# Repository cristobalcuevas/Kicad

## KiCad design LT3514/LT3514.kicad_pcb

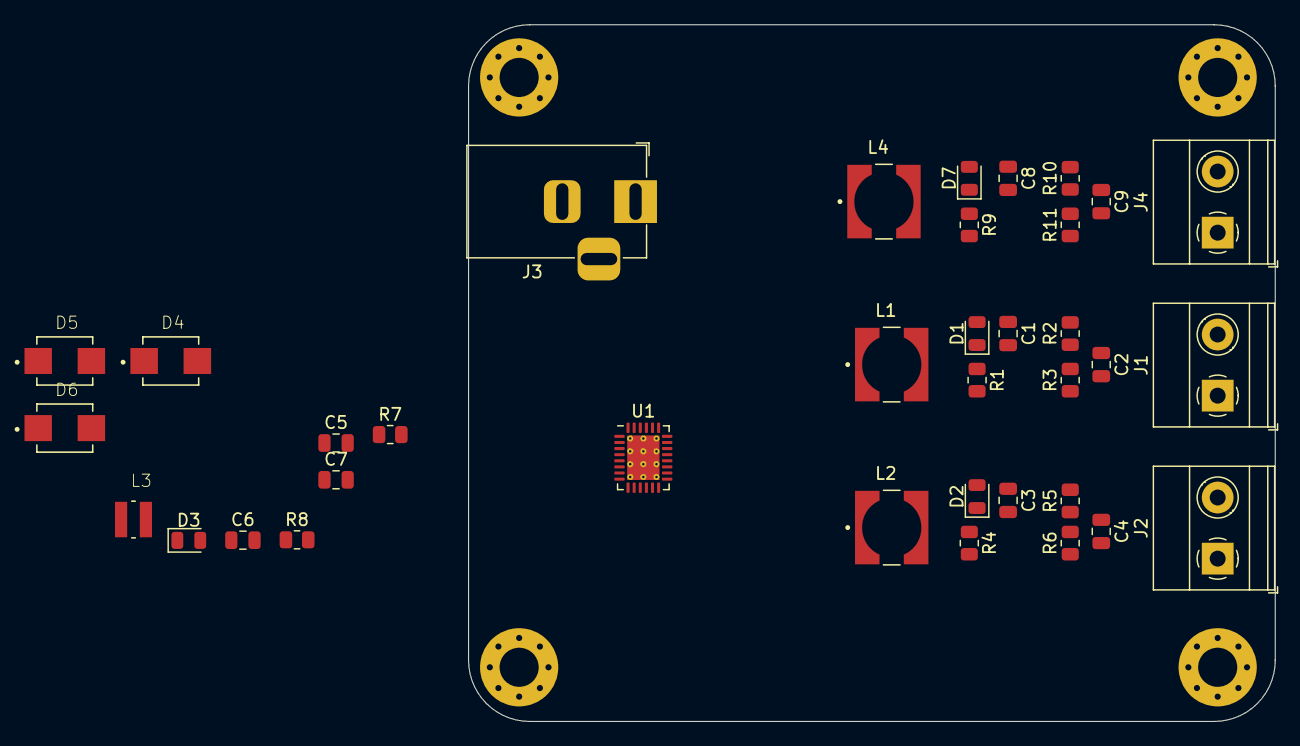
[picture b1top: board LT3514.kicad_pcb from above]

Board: 2 copper layers, 66.0 x 57.0 mm, 40 parts (0 on the bottom side), 23 nets, no tracks yet.

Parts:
C1: 47p; C_0805_2012Metric
C2: 47u; C_0805_2012Metric
C3: 22p; C_0805_2012Metric
C4, C9: 22u; C_0805_2012Metric
C5, C7: 1u; C_0805_2012Metric
C6: 47n; C_0805_2012Metric
C8: 100p; C_0805_2012Metric
D1, D2, D7: LED; LED_0805_2012Metric
D3: LED_Small; LED_0805_2012Metric
D4, D5, D6: D_Schottky_Small; B290
H1, H2, H3, H4: MountingHole; MountingHole_3.2mm_M3_Pad_Via
J1: OUT2; TerminalBlock_Phoenix_MKDS-1,5-2_1x02_P5.00mm_Horizontal
J2: OUT3; TerminalBlock_Phoenix_MKDS-1,5-2_1x02_P5.00mm_Horizontal
J3: Barrel_Jack_Switch; BarrelJack_Horizontal
J4: OUT1; TerminalBlock_Phoenix_MKDS-1,5-2_1x02_P5.00mm_Horizontal
L1: 4.7u; MSS6132
L2: 8.2u; MSS6132
L3: 10u; EPL3015
L4: 3.3u; MSS6132
R1, R4, R7, R9: 2k; R_0805_2012Metric
R2: 31.6k; R_0805_2012Metric
R3, R6, R11: 10.2k; R_0805_2012Metric
R5: 53.6k; R_0805_2012Metric
R8: 18.2k; R_0805_2012Metric
R10: 12.7k; R_0805_2012Metric
U1: LT3514xUFD; QFN-28-1EP_4x5mm_P0.5mm_EP2.65x3.65mm_ThermalVias

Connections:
+1V8: C8.1, C9.1, D7.2, J4.2, L4.2, R10.2
+3V3: C1.1, C2.1, D1.2, J1.2, L1.2, R2.2
+5V: C3.1, C4.1, D2.2, J2.2, L2.2, R5.2
+12V: C5.1, C7.2, J3.1, L3.1, R7.1, U1.9, U1.11, U1.16, U1.26, U1.28
/1V8/FB1: C8.2, R10.1, R11.2, U1.20
/1V8/SW1: D4.1, L4.1, U1.5
/3V3/FB3: C1.2, R2.1, R3.2, U1.21
/3V3/SW3: D5.1, L1.1, U1.4
/5V0/FB4: C3.2, R5.1, R6.2, U1.19
/5V0/SW4: D6.1, L2.1, U1.7
GND: C2.2, C4.2, C5.2, C6.2, C9.2, J1.1, J2.1, J3.2, J3.3, J4.1, R1.2, R3.1, R4.2, R6.1, R8.1, R9.2, R11.1, U1.10, U1.18, U1.27, U1.29
unnamed: C6.1, U1.12, U1.13, U1.15
unnamed: C7.1, U1.25
unnamed: D1.1, R1.1
unnamed: D2.1, R4.1
unnamed: D3.1, U1.23
unnamed: D3.2, R7.2
unnamed: D4.2, U1.6
unnamed: D5.2, U1.3
unnamed: D6.2, U1.8
unnamed: D7.1, R9.1
unnamed: L3.2, U1.24
unnamed: R8.2, U1.17

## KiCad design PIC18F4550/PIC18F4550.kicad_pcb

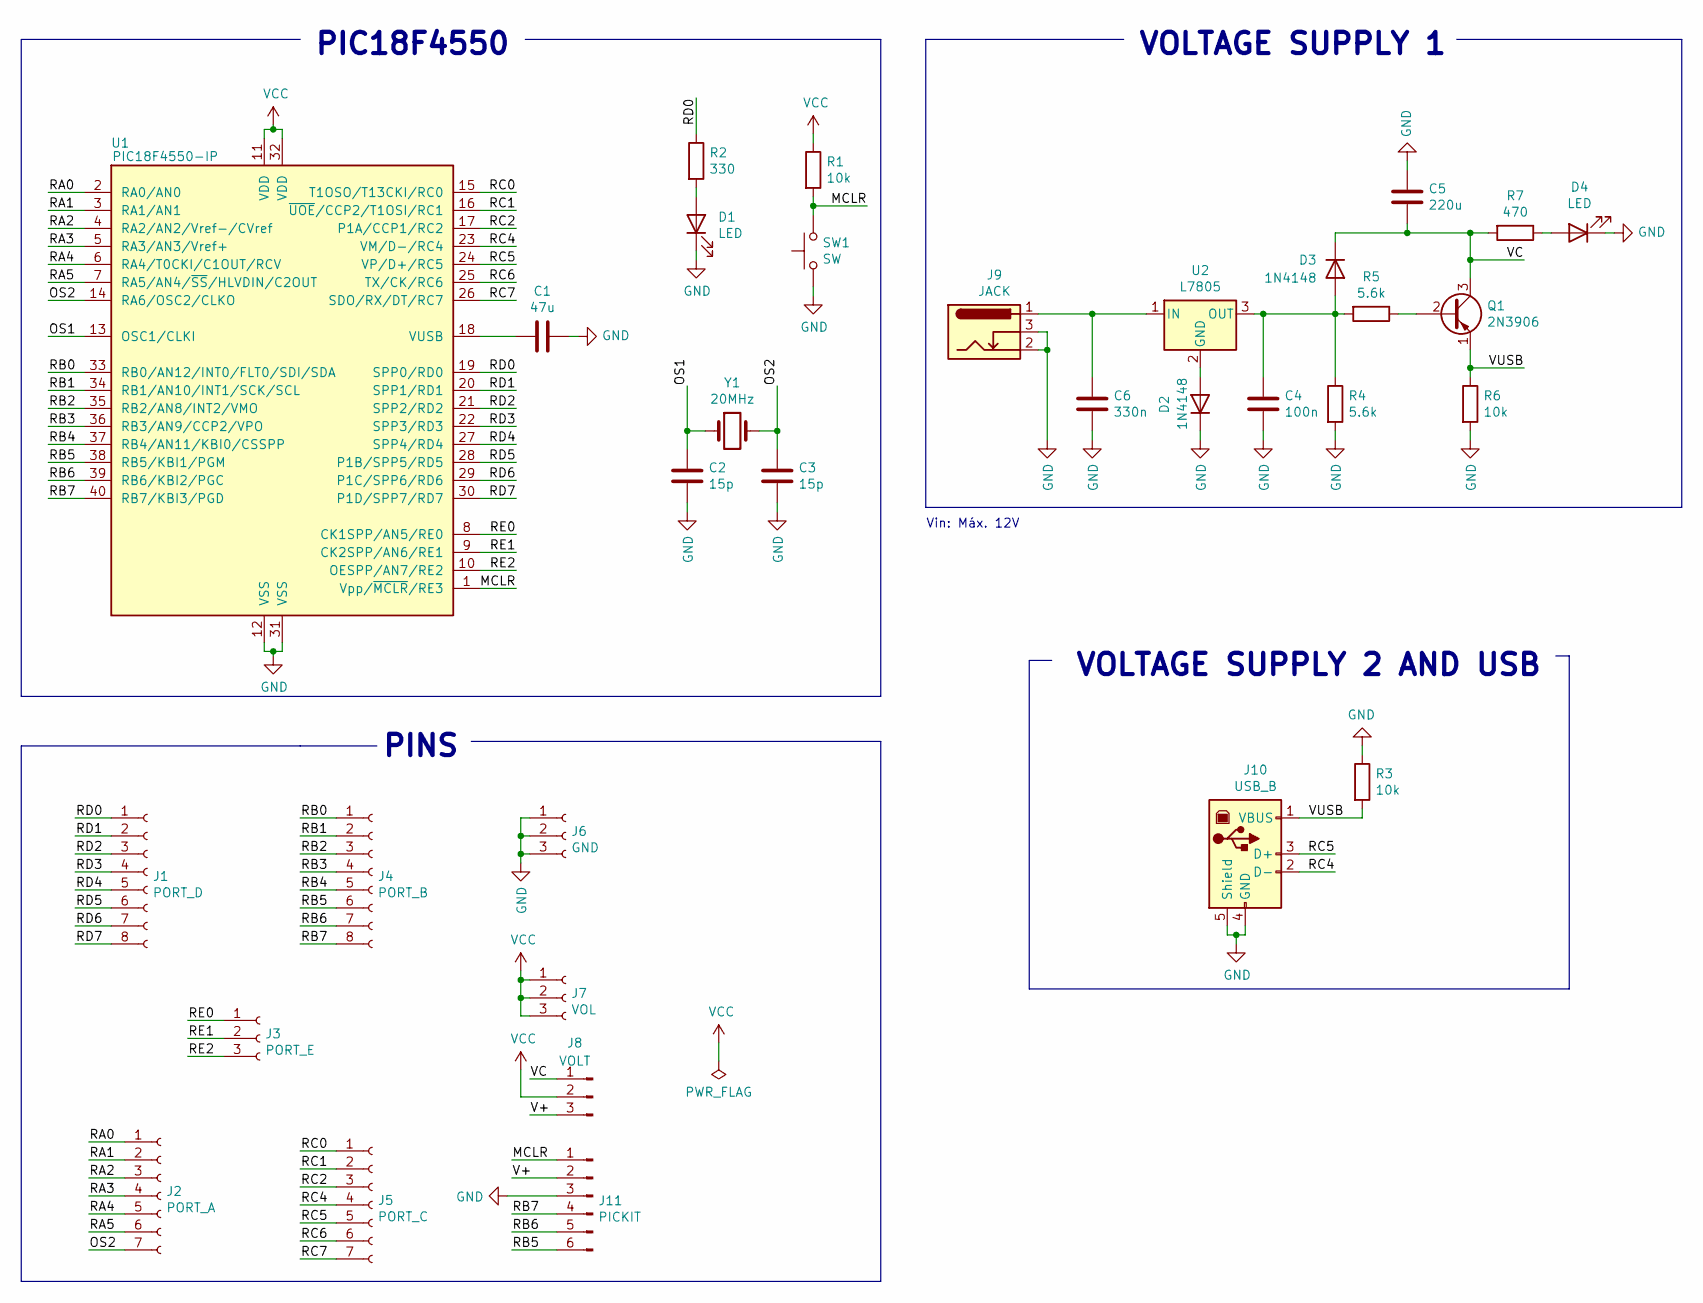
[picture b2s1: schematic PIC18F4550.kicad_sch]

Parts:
C1: 47u; CP_Radial_D6.3mm_P2.50mm
C2, C3: 15p; C_Disc_D3.8mm_W2.6mm_P2.50mm
C4: 100n; C_Disc_D3.8mm_W2.6mm_P2.50mm
C5: 220u; CP_Radial_D10.0mm_P2.50mm
C6: 330n; C_Disc_D3.8mm_W2.6mm_P2.50mm
D1, D4: LED; LED_D5.0mm
D2, D3: 1N4148; D_DO-35_SOD27_P7.62mm_Horizontal
J1: PORT_D; PinSocket_1x08_P2.54mm_Vertical
J2: PORT_A; PinSocket_1x07_P2.54mm_Vertical
J3: PORT_E; PinSocket_1x03_P2.54mm_Vertical
J4: PORT_B; PinSocket_1x08_P2.54mm_Vertical
J5: PORT_C; PinSocket_1x07_P2.54mm_Vertical
J6: GND; PinSocket_1x03_P2.54mm_Vertical
J7: VOL; PinSocket_1x03_P2.54mm_Vertical
J8: VOLT; PinHeader_1x03_P2.54mm_Vertical
J9: JACK; BarrelJack_Horizontal
J10: USB_B; USB_B_OST_USB-B1HSxx_Horizontal
J11: PICKIT; PinHeader_1x06_P2.54mm_Vertical
Q1: 2N3906; TO-92_Inline
R1, R3, R6: 10k; R_Axial_DIN0207_L6.3mm_D2.5mm_P7.62mm_Horizontal
R2: 330; R_Axial_DIN0207_L6.3mm_D2.5mm_P7.62mm_Horizontal
R4, R5: 5.6k; R_Axial_DIN0207_L6.3mm_D2.5mm_P7.62mm_Horizontal
R7: 470; R_Axial_DIN0207_L6.3mm_D2.5mm_P7.62mm_Horizontal
SW1: SW; SW_PUSH_6mm
U1: PIC18F4550-IP; DIP-40_W15.24mm
U2: L7805; TO-220-3_Vertical
Y1: 20MHz; Crystal_HC50_Vertical

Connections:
/MCLR: J11.1, R1.2, SW1.2, U1.1 (Vpp/~MCLR/RE3)
/OS1: C2.1, U1.13 (OSC1/CLKI), Y1.1
/OS2: C3.1, J2.7, U1.14 (RA6/OSC2/CLKO), Y1.2
/RA0: J2.1, U1.2 (RA0/AN0)
/RA1: J2.2, U1.3 (RA1/AN1)
/RA2: J2.3, U1.4 (RA2/AN2/Vref-/CVref)
/RA3: J2.4, U1.5 (RA3/AN3/Vref+)
/RA4: J2.5, U1.6 (RA4/T0CKI/C1OUT/RCV)
/RA5: J2.6, U1.7 (RA5/AN4/~SS/HLVDIN/C2OUT)
/RB0: J4.1, U1.33 (RB0/AN12/INT0/FLT0/SDI/SDA)
/RB1: J4.2, U1.34 (RB1/AN10/INT1/SCK/SCL)
/RB2: J4.3, U1.35 (RB2/AN8/INT2/VMO)
/RB3: J4.4, U1.36 (RB3/AN9/CCP2/VPO)
/RB4: J4.5, U1.37 (RB4/AN11/KBI0/CSSPP)
/RB5: J4.6, J11.6, U1.38 (RB5/KBI1/PGM)
/RB6: J4.7, J11.5, U1.39 (RB6/KBI2/PGC)
/RB7: J4.8, J11.4, U1.40 (RB7/KBI3/PGD)
/RC0: J5.1, U1.15 (T1OSO/T13CKI/RC0)
/RC1: J5.2, U1.16 (~UOE/CCP2/T1OSI/RC1)
/RC2: J5.3, U1.17 (P1A/CCP1/RC2)
/RC4: J5.4, J10.2 (D-), U1.23 (VM/D-/RC4)
/RC5: J5.5, J10.3 (D+), U1.24 (VP/D+/RC5)
/RC6: J5.6, U1.25 (TX/CK/RC6)
/RC7: J5.7, U1.26 (SDO/RX/DT/RC7)
/RD0: J1.1, R2.1, U1.19 (SPP0/RD0)
/RD1: J1.2, U1.20 (SPP1/RD1)
/RD2: J1.3, U1.21 (SPP2/RD2)
/RD3: J1.4, U1.22 (SPP3/RD3)
/RD4: J1.5, U1.27 (SPP4/RD4)
/RD5: J1.6, U1.28 (P1B/SPP5/RD5)
/RD6: J1.7, U1.29 (P1C/SPP6/RD6)
/RD7: J1.8, U1.30 (P1D/SPP7/RD7)
/RE0: J3.1, U1.8 (CK1SPP/AN5/RE0)
/RE1: J3.2, U1.9 (CK2SPP/AN6/RE1)
/RE2: J3.3, U1.10 (OESPP/AN7/RE2)
/V+: J8.3, J11.2
/VC: C5.2, D3.1 (K), J8.1, Q1.3 (C), R7.2
/VUSB: J10.1 (VBUS), Q1.1 (E), R3.2, R6.1
GND: C1.1, C2.2, C3.2, C4.2, C5.1, C6.2, D1.1 (K), D2.1 (K), D4.1 (K), J6.1, J6.2, J6.3, J9.2, J9.3, J10.4 (GND), J10.5 (Shield), J11.3, R3.1, R4.2, R6.2, SW1.1, U1.12 (VSS), U1.31 (VSS)
unnamed: C1.2, U1.18 (VUSB)
unnamed: C4.1, D3.2 (A), R4.1, R5.2, U2.3 (OUT)
unnamed: C6.1, J9.1, U2.1 (IN)
unnamed: D1.2 (A), R2.2
unnamed: D2.2 (A), U2.2 (GND)
unnamed: D4.2 (A), R7.1
unnamed: Q1.2 (B), R5.1
VCC: J7.1, J7.2, J7.3, J8.2, R1.1, U1.11 (VDD), U1.32 (VDD)

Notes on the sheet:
PINS
Vin: Máx. 12V
VOLTAGE SUPPLY 1
VOLTAGE SUPPLY 2 AND USB
PIC18F4550

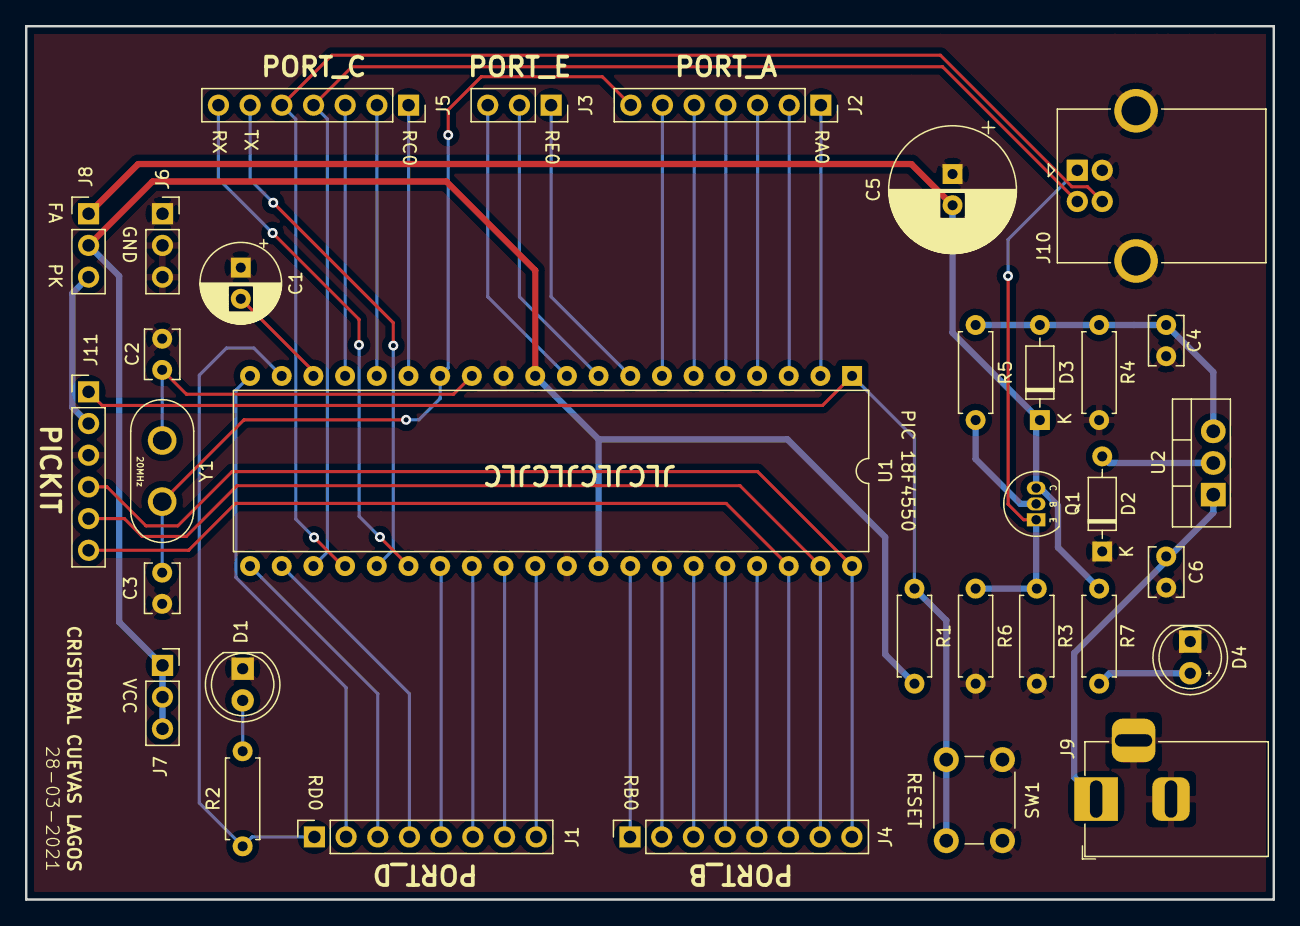
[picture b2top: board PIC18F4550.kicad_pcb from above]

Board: 2 copper layers, 100.0 x 70.0 mm, 33 parts (0 on the bottom side), 47 nets.

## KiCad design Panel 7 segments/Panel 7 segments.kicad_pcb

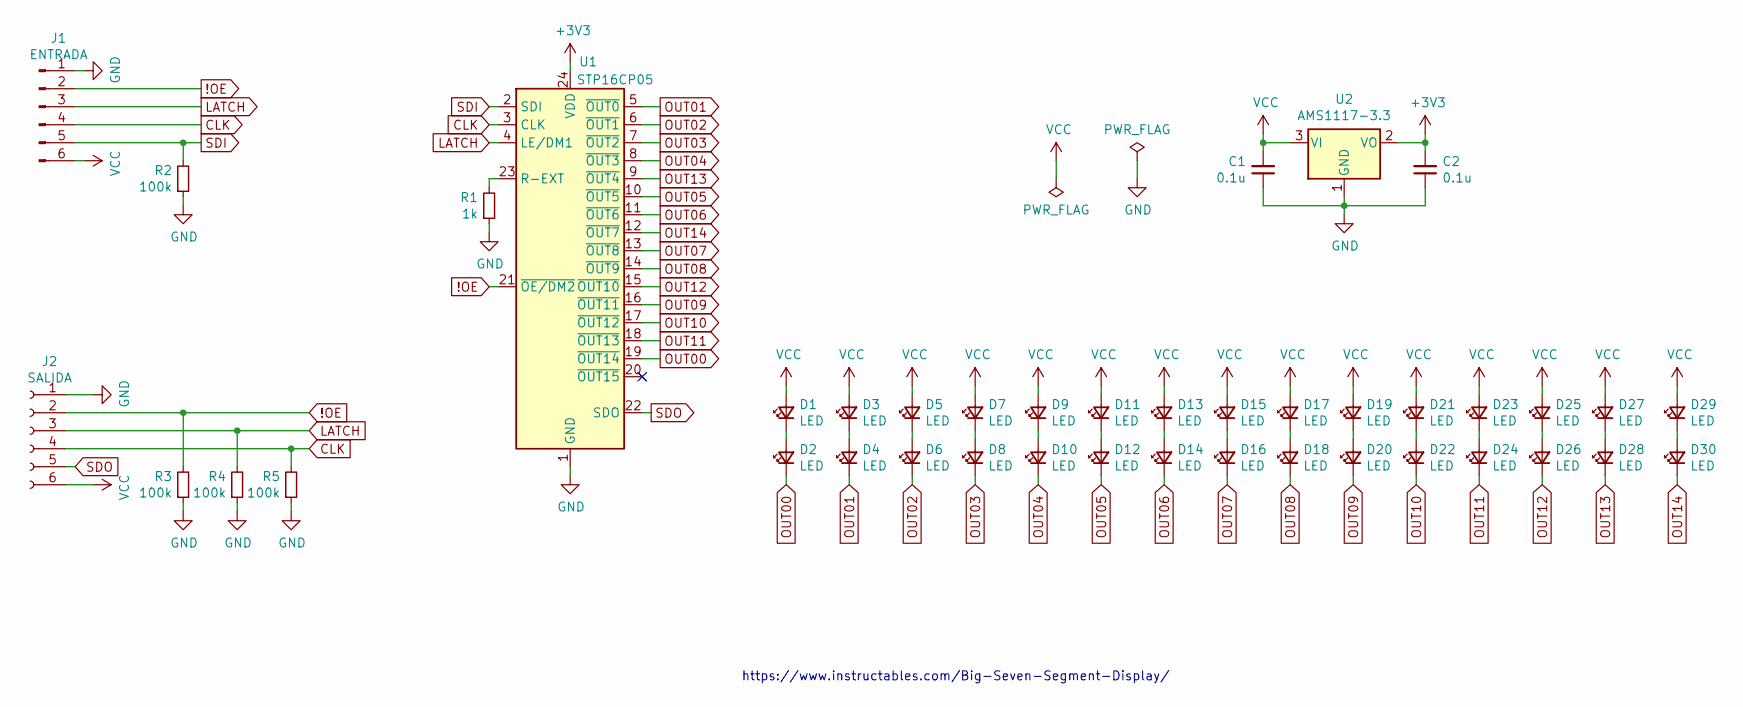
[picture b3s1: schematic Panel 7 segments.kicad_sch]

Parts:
C1, C2: 0.1u; C_1206_3216Metric
D1, D2, D3, D4, D5, D6, D7, D8, D9, D10, D11, D12, D13, D14, D15, D16, D17, D18, D19, D20, D21, D22, D23, D24, D25, D26, D27, D28, D29, D30: LED; LED_2010_5025Metric
J1: ENTRADA; PinHeader_1x06_P2.54mm_Horizontal
J2: SALIDA; PinSocket_1x06_P2.54mm_Horizontal
R1: 1k; R_1206_3216Metric
R2, R3, R4, R5: 100k; R_1206_3216Metric
U1: STP16CP05; TSSOP-24_4.4x7.8mm_P0.65mm
U2: AMS1117-3.3; SOT-223-3_TabPin2

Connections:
!OE: J1.2, J2.2, R3.2, U1.21 (~OE/DM2)
+3V3: C2.2, U1.24 (VDD), U2.2 (VO)
CLK: J1.4, J2.4, R5.2, U1.3 (CLK)
GND: C1.1, C2.1, J1.1, J2.1, R1.1, R2.1, R3.1, R4.1, R5.1, U1.1 (GND), U2.1 (GND)
LATCH: J1.3, J2.3, R4.2, U1.4 (LE/DM1)
unnamed: D1.1 (K), D2.2 (A)
unnamed: D3.1 (K), D4.2 (A)
unnamed: D5.1 (K), D6.2 (A)
unnamed: D7.1 (K), D8.2 (A)
unnamed: D9.1 (K), D10.2 (A)
unnamed: D11.1 (K), D12.2 (A)
unnamed: D13.1 (K), D14.2 (A)
unnamed: D15.1 (K), D16.2 (A)
unnamed: D17.1 (K), D18.2 (A)
unnamed: D19.1 (K), D20.2 (A)
unnamed: D21.1 (K), D22.2 (A)
unnamed: D23.1 (K), D24.2 (A)
unnamed: D25.1 (K), D26.2 (A)
unnamed: D27.1 (K), D28.2 (A)
unnamed: D29.1 (K), D30.2 (A)
unnamed: R1.2, U1.23 (R-EXT)
OUT00: D2.1 (K), U1.19 (~OUT14)
OUT01: D4.1 (K), U1.5 (~OUT0)
OUT02: D6.1 (K), U1.6 (~OUT1)
OUT03: D8.1 (K), U1.7 (~OUT2)
OUT04: D10.1 (K), U1.8 (~OUT3)
OUT05: D12.1 (K), U1.10 (~OUT5)
OUT06: D14.1 (K), U1.11 (~OUT6)
OUT07: D16.1 (K), U1.13 (~OUT8)
OUT08: D18.1 (K), U1.14 (~OUT9)
OUT09: D20.1 (K), U1.16 (~OUT11)
OUT10: D22.1 (K), U1.17 (~OUT12)
OUT11: D24.1 (K), U1.18 (~OUT13)
OUT12: D26.1 (K), U1.15 (~OUT10)
OUT13: D28.1 (K), U1.9 (~OUT4)
OUT14: D30.1 (K), U1.12 (~OUT7)
SDI: J1.5, R2.2, U1.2 (SDI)
SDO: J2.5, U1.22 (SDO)
VCC: C1.2, D1.2 (A), D3.2 (A), D5.2 (A), D7.2 (A), D9.2 (A), D11.2 (A), D13.2 (A), D15.2 (A), D17.2 (A), D19.2 (A), D21.2 (A), D23.2 (A), D25.2 (A), D27.2 (A), D29.2 (A), J1.6, J2.6, U2.3 (VI)

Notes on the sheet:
https://www.instructables.com/Big-Seven-Segment-Display/

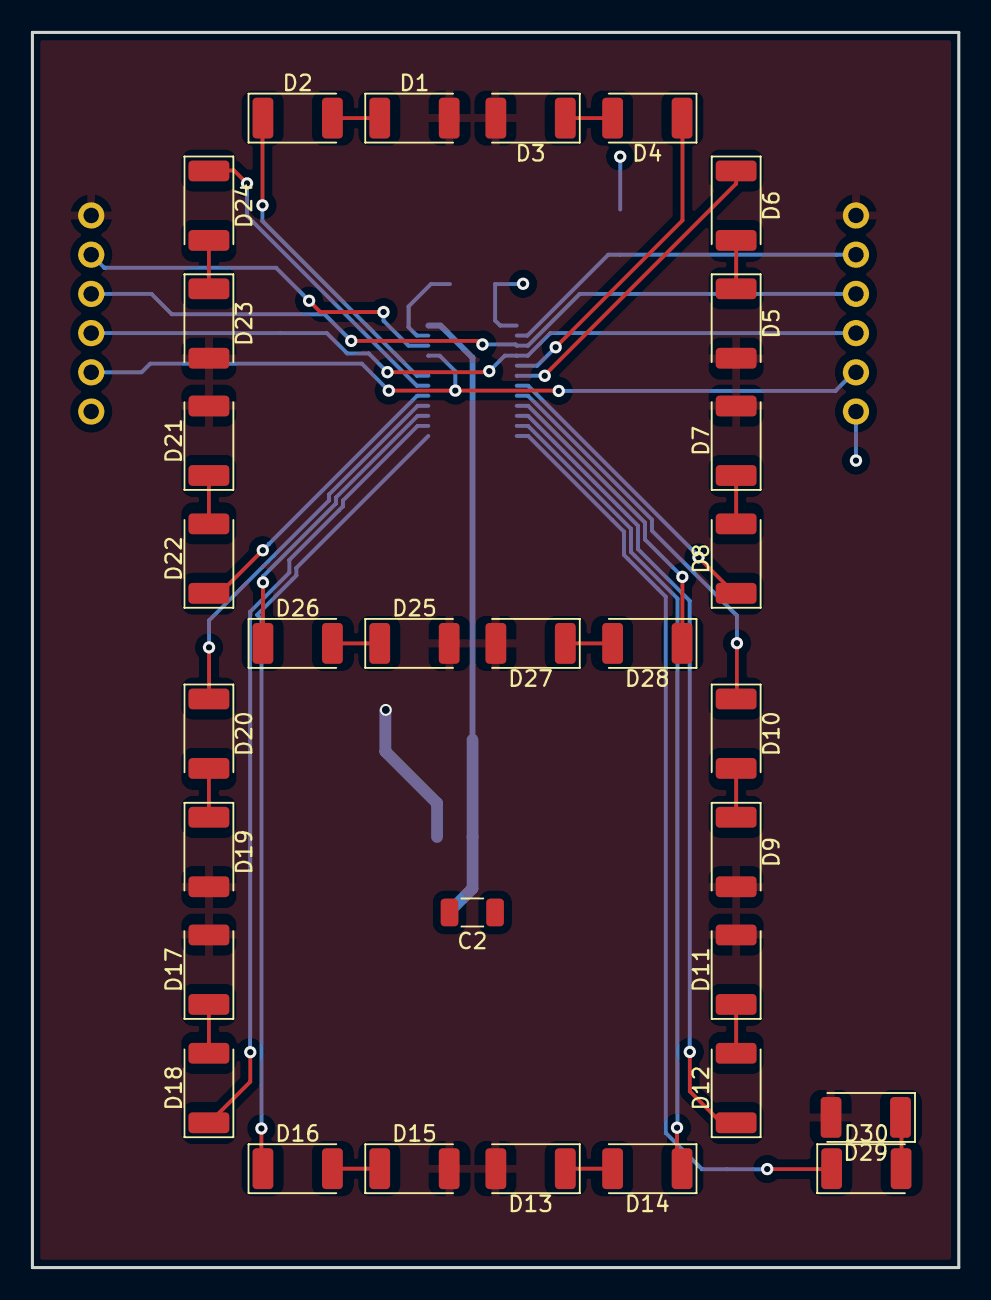
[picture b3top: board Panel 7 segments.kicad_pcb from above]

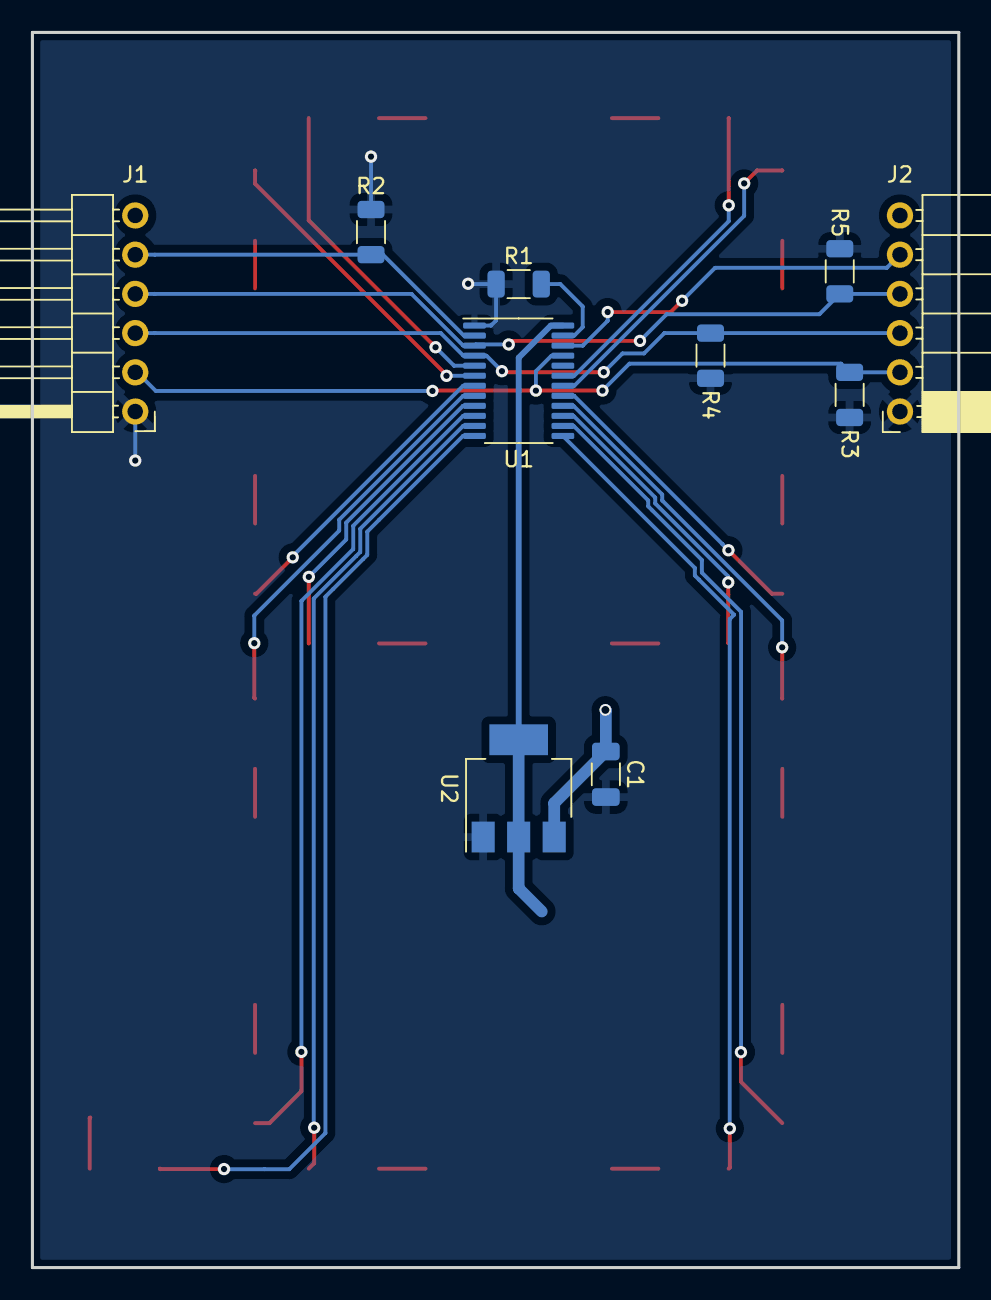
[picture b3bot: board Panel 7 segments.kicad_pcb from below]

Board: 2 copper layers, 60.0 x 80.0 mm, 41 parts (10 on the bottom side), 39 nets.

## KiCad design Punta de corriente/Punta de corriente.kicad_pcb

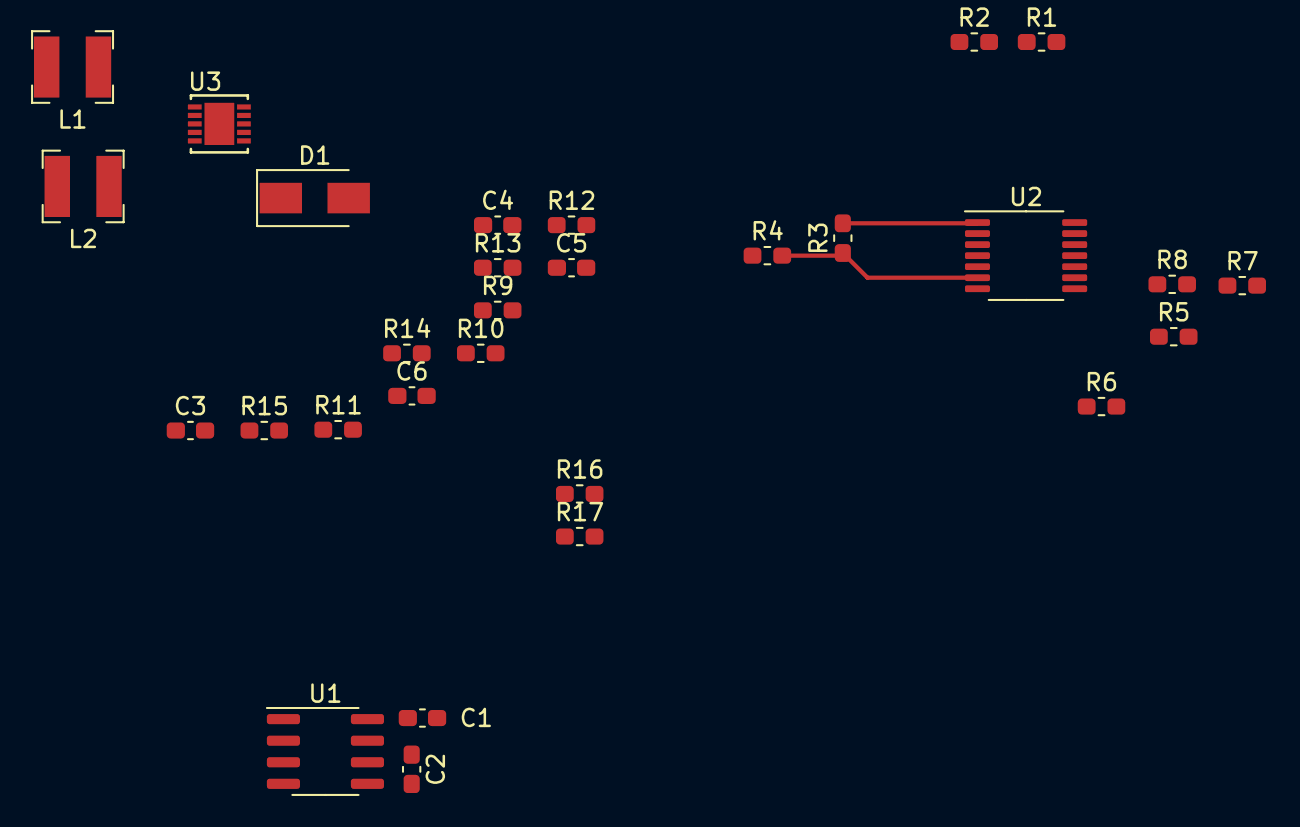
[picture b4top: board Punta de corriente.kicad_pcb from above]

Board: 2 copper layers, 29 parts (0 on the bottom side), 24 nets.

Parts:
C1, C4: 100n; C_0603_1608Metric_Pad1.08x0.95mm_HandSolder
C2: 1n; C_0603_1608Metric_Pad1.08x0.95mm_HandSolder
C3: 1u; C_0603_1608Metric_Pad1.08x0.95mm_HandSolder
C5, C6: 0.47u; C_0603_1608Metric_Pad1.08x0.95mm_HandSolder
D1: Schottky; D_SMA
L1, L2: 10u; L_Bourns-SRN4018
R1, R2, R3, R4, R5, R6, R7, R8, R10, R14: 10k; R_0603_1608Metric_Pad1.05x0.95mm_HandSolder
R9, R11, R12, R13, R15: 1k; R_0603_1608Metric_Pad1.05x0.95mm_HandSolder
R16, R17: 5.1k; R_0603_1608Metric_Pad1.05x0.95mm_HandSolder
U1: ACS712xLCTR-05B; SOIC-8_3.9x4.9mm_P1.27mm
U2: ADA4807-4; TSSOP-14_4.4x5mm_P0.65mm
U3: LT3463EDDPBF; DFN-10_DD

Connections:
/Amplificador operacional/+5V: C1.2, C3.2, L1.1, L2.1, R1.2, U1.8, U3.3, U3.8, U3.9
/Amplificador operacional/+15V: C6.1, R10.2, U2.4, U3.1
/Amplificador operacional/-15V: C5.1, D1.2, R14.1, U2.11
/Amplificador operacional/VOUT: U1.7, U2.2
/Fuenta de voltaje/SW2: C4.1, L1.2, U3.4
GND: C1.1, C2.2, C3.1, C5.2, C6.2, R2.1, R4.1, R7.2, R15.1, R16.2, R17.2, U1.5, U3.11
unnamed: C2.1, U1.6
unnamed: C4.2, D1.1, U3.5
unnamed: U1.3, U1.4
unnamed: U1.1, U1.2
unnamed: R8.1, U2.8
unnamed: L2.2, U3.2
unnamed: R3.1, R4.2, U2.6
unnamed: R3.2, U2.1, U2.3
unnamed: R5.1, R6.2, U2.5
unnamed: R5.2, U2.12, U2.14
unnamed: R6.1, U2.7, U2.9
unnamed: R7.1, R8.2, U2.10
unnamed: R9.2, U3.7
unnamed: R10.1, R12.2
unnamed: R11.1, R13.2
unnamed: R9.1, R11.2, U3.6
unnamed: R12.1, R15.2, U3.10
unnamed: R13.1, R14.2

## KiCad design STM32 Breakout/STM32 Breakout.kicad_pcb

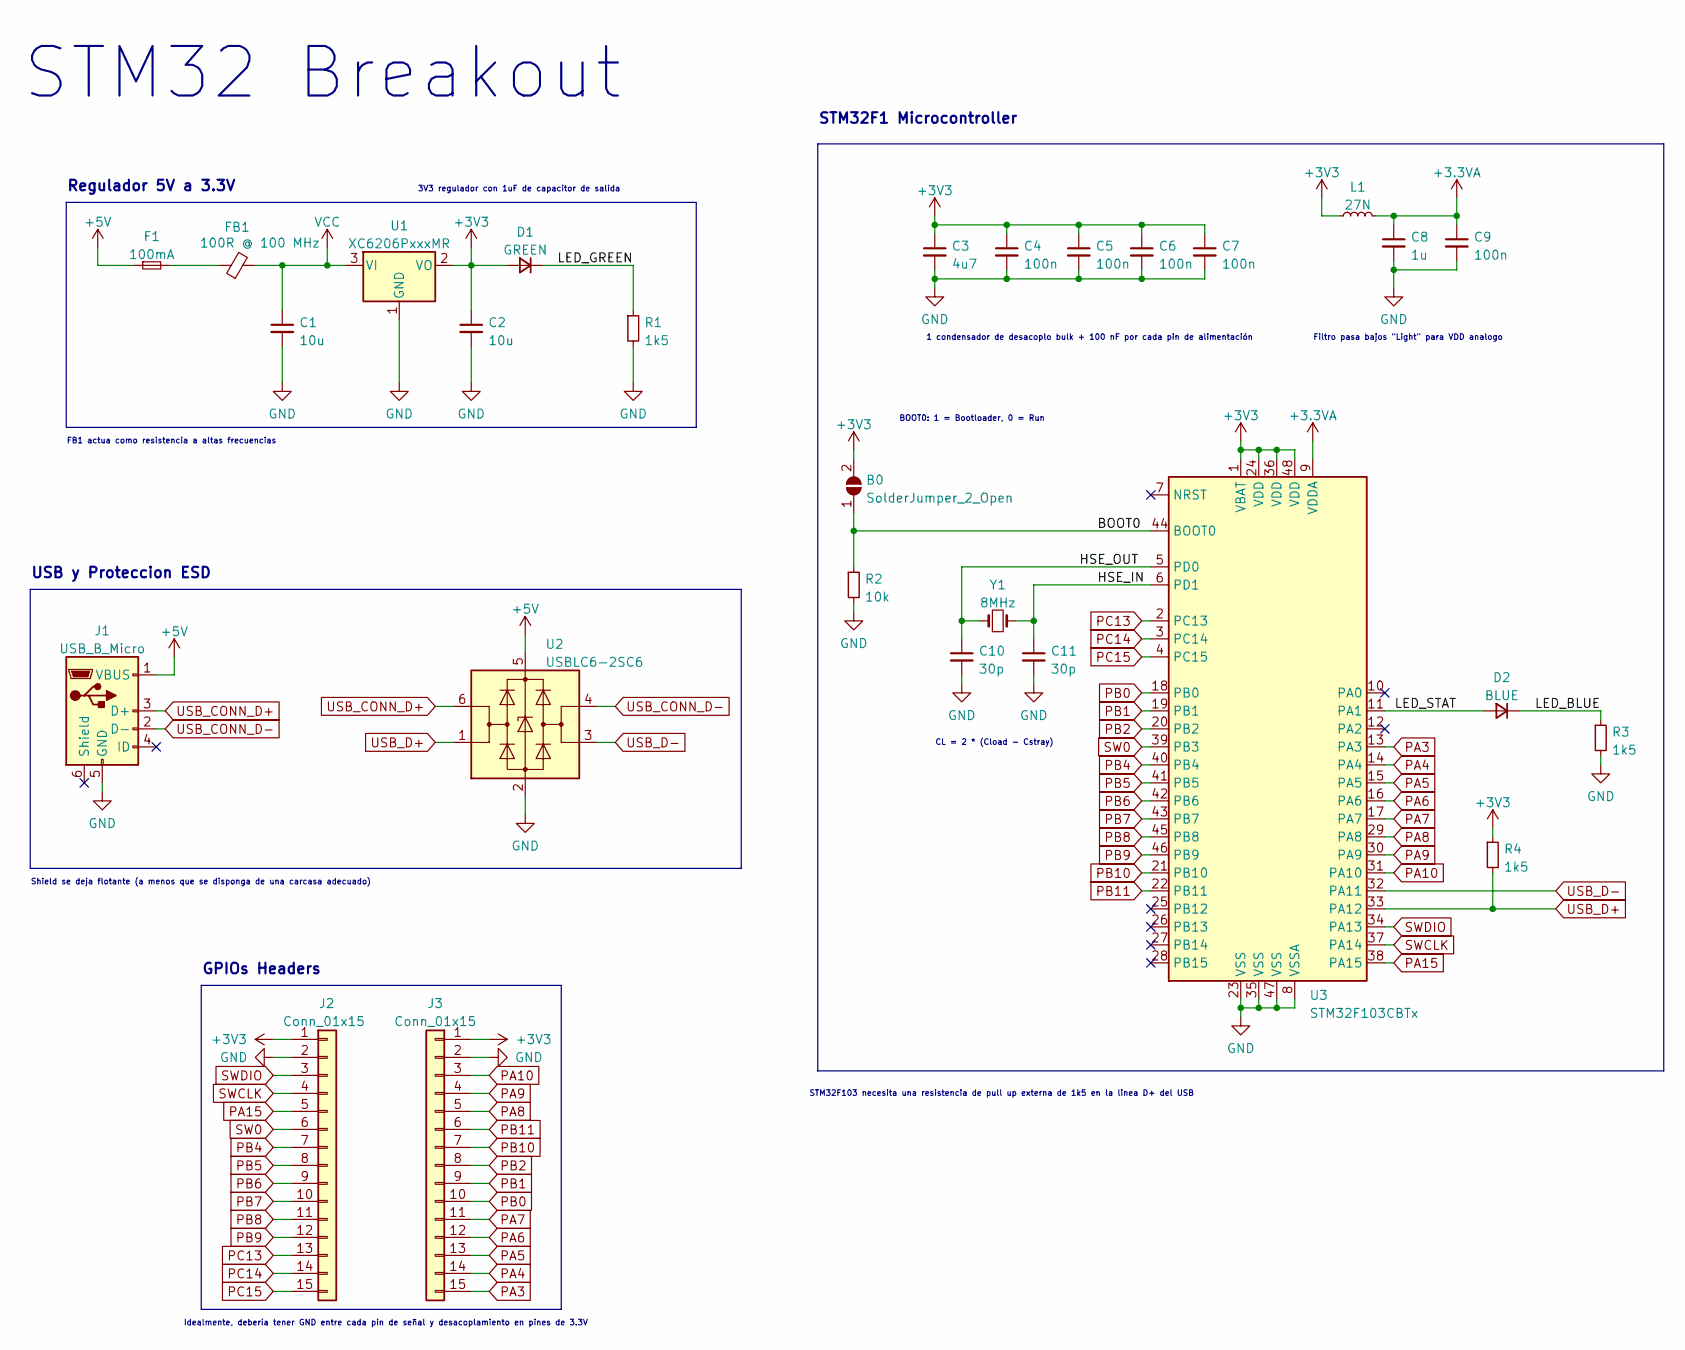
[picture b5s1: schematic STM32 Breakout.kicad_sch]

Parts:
B0: SolderJumper_2_Open; SolderJumper-2_P1.3mm_Open_Pad1.0x1.5mm
C1, C2: 10u; C_0603_1608Metric
C3: 4u7; C_0603_1608Metric
C4, C5, C6, C7, C9: 100n; C_0402_1005Metric
C8: 1u; C_0402_1005Metric
C10, C11: 30p; C_0402_1005Metric
D1: GREEN; LED_0603_1608Metric
D2: BLUE; LED_0603_1608Metric
F1: 100mA; Fuse_0603_1608Metric
FB1: 100R @ 100 MHz; L_0805_2012Metric
J1: USB_B_Micro; USB_Micro-B_Wuerth_629105150521
J2, J3: Conn_01x15; PinHeader_1x15_P2.54mm_Vertical
L1: 27N; L_0402_1005Metric
R1, R3: 1k5; R_0603_1608Metric
R2: 10k; R_0402_1005Metric
R4: 1k5; R_0402_1005Metric
U1: XC6206PxxxMR; SOT-23
U2: USBLC6-2SC6; SOT-23-6
U3: STM32F103CBTx; LQFP-48_7x7mm_P0.5mm
Y1: 8MHz; Crystal_SMD_5032-2Pin_5.0x3.2mm

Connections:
+3.3VA: C8.1, C9.1, L1.2, U3.9 (VDDA)
+3V3: B0.2 (B), C2.1, C3.1, C4.1, C5.1, C6.1, C7.1, D1.2 (A), J2.1, J3.1, L1.1, R4.1, U1.2 (VO), U3.1 (VBAT), U3.24 (VDD), U3.36 (VDD), U3.48 (VDD)
+5V: F1.1, J1.1 (VBUS), U2.5 (VBUS)
/BOOT0: B0.1 (A), R2.1, U3.44 (BOOT0)
/HSE_IN: C11.1, U3.6 (PD1), Y1.2
/HSE_OUT: C10.1, U3.5 (PD0), Y1.1
/LED_BLUE: D2.1 (K), R3.1
/LED_GREEN: D1.1 (K), R1.1
/LED_STAT: D2.2 (A), U3.11 (PA1)
GND: C1.2, C2.2, C3.2, C4.2, C5.2, C6.2, C7.2, C8.2, C9.2, C10.2, C11.2, J1.5 (GND), J2.2, J3.2, R1.2, R2.2, R3.2, U1.1 (GND), U2.2 (GND), U3.8 (VSSA), U3.23 (VSS), U3.35 (VSS), U3.47 (VSS)
unnamed: F1.2, FB1.1
PA3: J3.15, U3.13 (PA3)
PA4: J3.14, U3.14 (PA4)
PA5: J3.13, U3.15 (PA5)
PA6: J3.12, U3.16 (PA6)
PA7: J3.11, U3.17 (PA7)
PA8: J3.5, U3.29 (PA8)
PA9: J3.4, U3.30 (PA9)
PA10: J3.3, U3.31 (PA10)
PA15: J2.5, U3.38 (PA15)
PB0: J3.10, U3.18 (PB0)
PB1: J3.9, U3.19 (PB1)
PB2: J3.8, U3.20 (PB2)
PB4: J2.7, U3.40 (PB4)
PB5: J2.8, U3.41 (PB5)
PB6: J2.9, U3.42 (PB6)
PB7: J2.10, U3.43 (PB7)
PB8: J2.11, U3.45 (PB8)
PB9: J2.12, U3.46 (PB9)
PB10: J3.7, U3.21 (PB10)
PB11: J3.6, U3.22 (PB11)
PC13: J2.13, U3.2 (PC13)
PC14: J2.14, U3.3 (PC14)
PC15: J2.15, U3.4 (PC15)
SW0: J2.6, U3.39 (PB3)
SWCLK: J2.4, U3.37 (PA14)
SWDIO: J2.3, U3.34 (PA13)
USB_CONN_D+: J1.3 (D+), U2.6 (I/O1)
USB_CONN_D-: J1.2 (D-), U2.4 (I/O2)
USB_D+: R4.2, U2.1 (I/O1), U3.33 (PA12)
USB_D-: U2.3 (I/O2), U3.32 (PA11)
VCC: C1.1, FB1.2, U1.3 (VI)

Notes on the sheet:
Regulador 5V a 3.3V
STM32F1 Microcontroller
STM32F103 necesita una resistencia de pull up externa de 1k5 en la linea D+ del USB
Filtro pasa bajos "Light" para VDD analogo
1 condensador de desacoplo bulk + 100 nF por cada pin de alimentación
FB1 actua como resistencia a altas frecuencias
CL = 2 * (Cload - Cstray)
Idealmente, debería tener GND entre cada pin de señal y desacoplamiento en pines de 3.3V
USB y Proteccion ESD
Shield se deja flotante (a menos que se disponga de una carcasa adecuado)
BOOT0: 1 = Bootloader, 0 = Run
STM32 Breakout
3V3 regulador con 1uF de capacitor de salida
GPIOs Headers

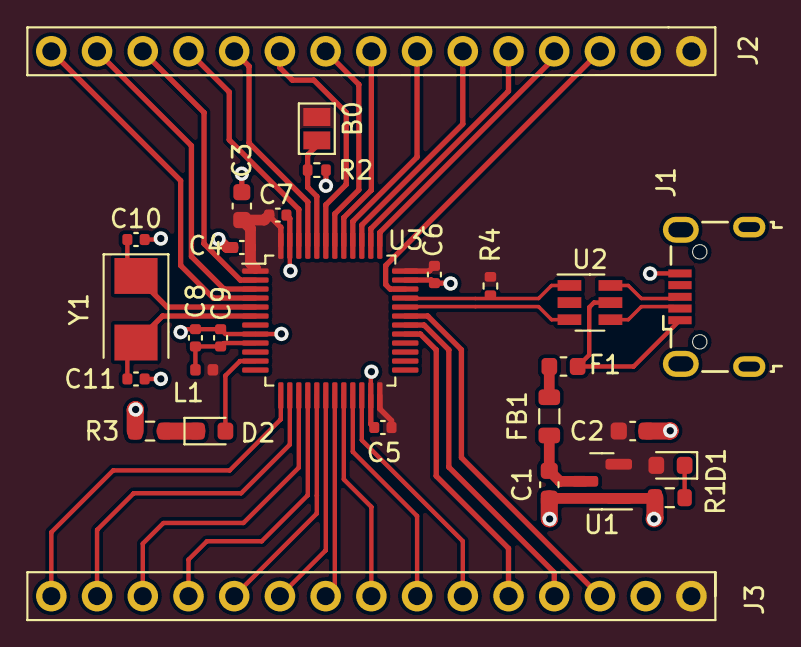
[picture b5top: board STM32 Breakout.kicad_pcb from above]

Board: 4 copper layers, 28 parts (0 on the bottom side), 42 nets.

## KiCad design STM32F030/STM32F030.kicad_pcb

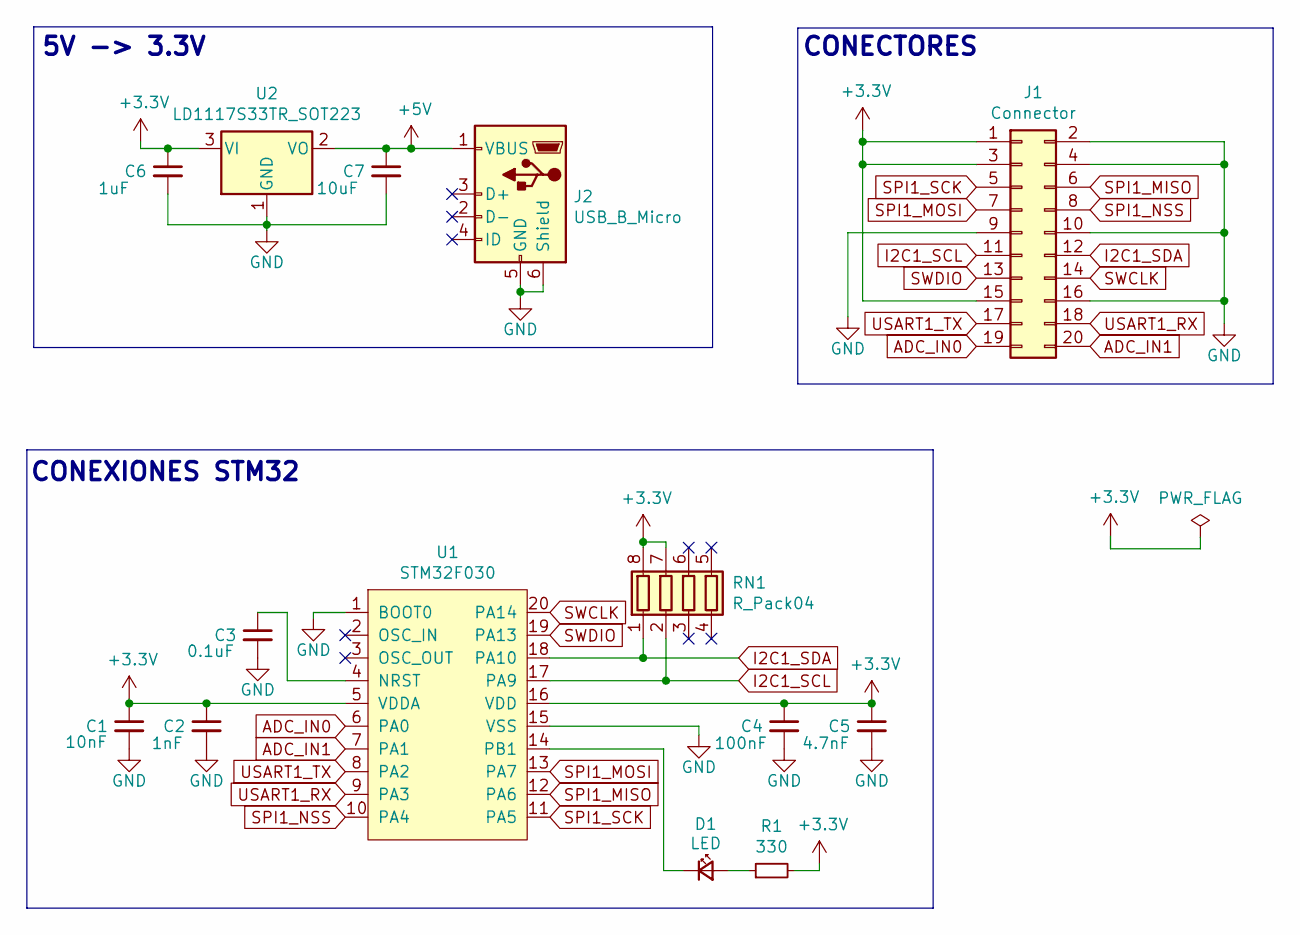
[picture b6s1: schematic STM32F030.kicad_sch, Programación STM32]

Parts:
C1: 10nF; C_0805_2012Metric_Pad1.15x1.40mm_HandSolder
C2: 1nF; C_0805_2012Metric_Pad1.15x1.40mm_HandSolder
C3: 0.1uF; C_0805_2012Metric_Pad1.15x1.40mm_HandSolder
C4: 100nF; C_0805_2012Metric_Pad1.15x1.40mm_HandSolder
C5: 4.7nF; C_0805_2012Metric_Pad1.15x1.40mm_HandSolder
C6: 1uF; C_0805_2012Metric_Pad1.15x1.40mm_HandSolder
C7: 10uF; C_0805_2012Metric_Pad1.15x1.40mm_HandSolder
D1: LED; LED_0805_2012Metric_Pad1.15x1.40mm_HandSolder
J1: Connector; PinHeader_2x10_P2.54mm_Vertical
J2: USB_B_Micro; USB_Micro-B_Molex-105017-0001
R1: 330; R_0805_2012Metric_Pad1.15x1.40mm_HandSolder
RN1: R_Pack04; R_Array_Convex_4x0603
U1: STM32F030; TSSOP-20_4.4x6.5mm_P0.65mm
U2: LD1117S33TR_SOT223; SOT-223-3_TabPin2

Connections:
+3V3: C1.1, C2.1, C4.1, C5.1, C6.1, J1.1, J1.3, J1.15, R1.2, RN1.7 (R2.2), RN1.8 (R1.2), U1.5 (VDDA), U1.16 (VDD), U2.3 (VI)
+5V: C7.1, J2.1 (VBUS), U2.2 (VO)
ADC_IN0: J1.19, U1.6 (PA0)
ADC_IN1: J1.20, U1.7 (PA1)
GND: C1.2, C2.2, C3.2, C4.2, C5.2, C6.2, C7.2, J1.2, J1.4, J1.9, J1.10, J1.16, J2.5 (GND), J2.6 (Shield), U1.1 (BOOT0), U1.15 (VSS), U2.1 (GND)
I2C1_SCL: J1.11, RN1.2 (R2.1), U1.17 (PA9)
I2C1_SDA: J1.12, RN1.1 (R1.1), U1.18 (PA10)
unnamed: C3.1, U1.4 (NRST)
unnamed: D1.1 (K), U1.14 (PB1)
unnamed: D1.2 (A), R1.1
SPI1_MISO: J1.6, U1.12 (PA6)
SPI1_MOSI: J1.7, U1.13 (PA7)
SPI1_NSS: J1.8, U1.10 (PA4)
SPI1_SCK: J1.5, U1.11 (PA5)
SWCLK: J1.14, U1.20 (PA14)
SWDIO: J1.13, U1.19 (PA13)
USART1_RX: J1.18, U1.9 (PA3)
USART1_TX: J1.17, U1.8 (PA2)

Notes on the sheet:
CONEXIONES STM32
5V -> 3.3V
CONECTORES

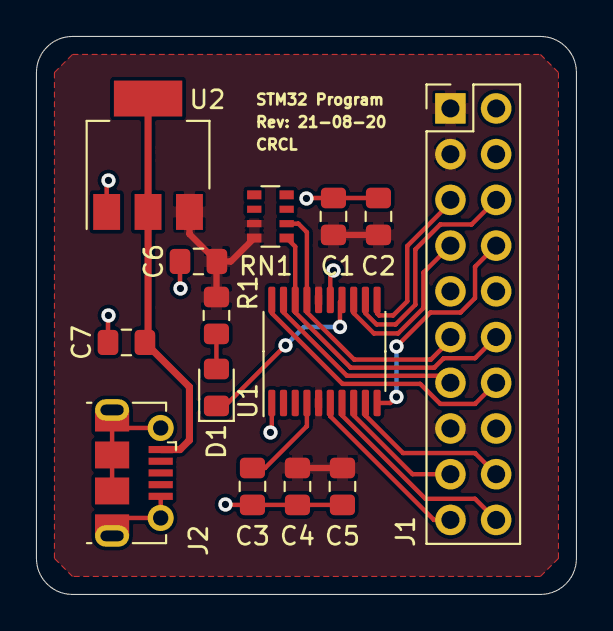
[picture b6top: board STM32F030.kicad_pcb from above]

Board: 2 copper layers, 30.0 x 31.0 mm, 14 parts (0 on the bottom side), 18 nets.
